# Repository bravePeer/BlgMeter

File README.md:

# BLGmeter
Device that can measure glucose in wort.

Used library to redirect website:
https://github.com/electronicsguy/HTTPSRedirect

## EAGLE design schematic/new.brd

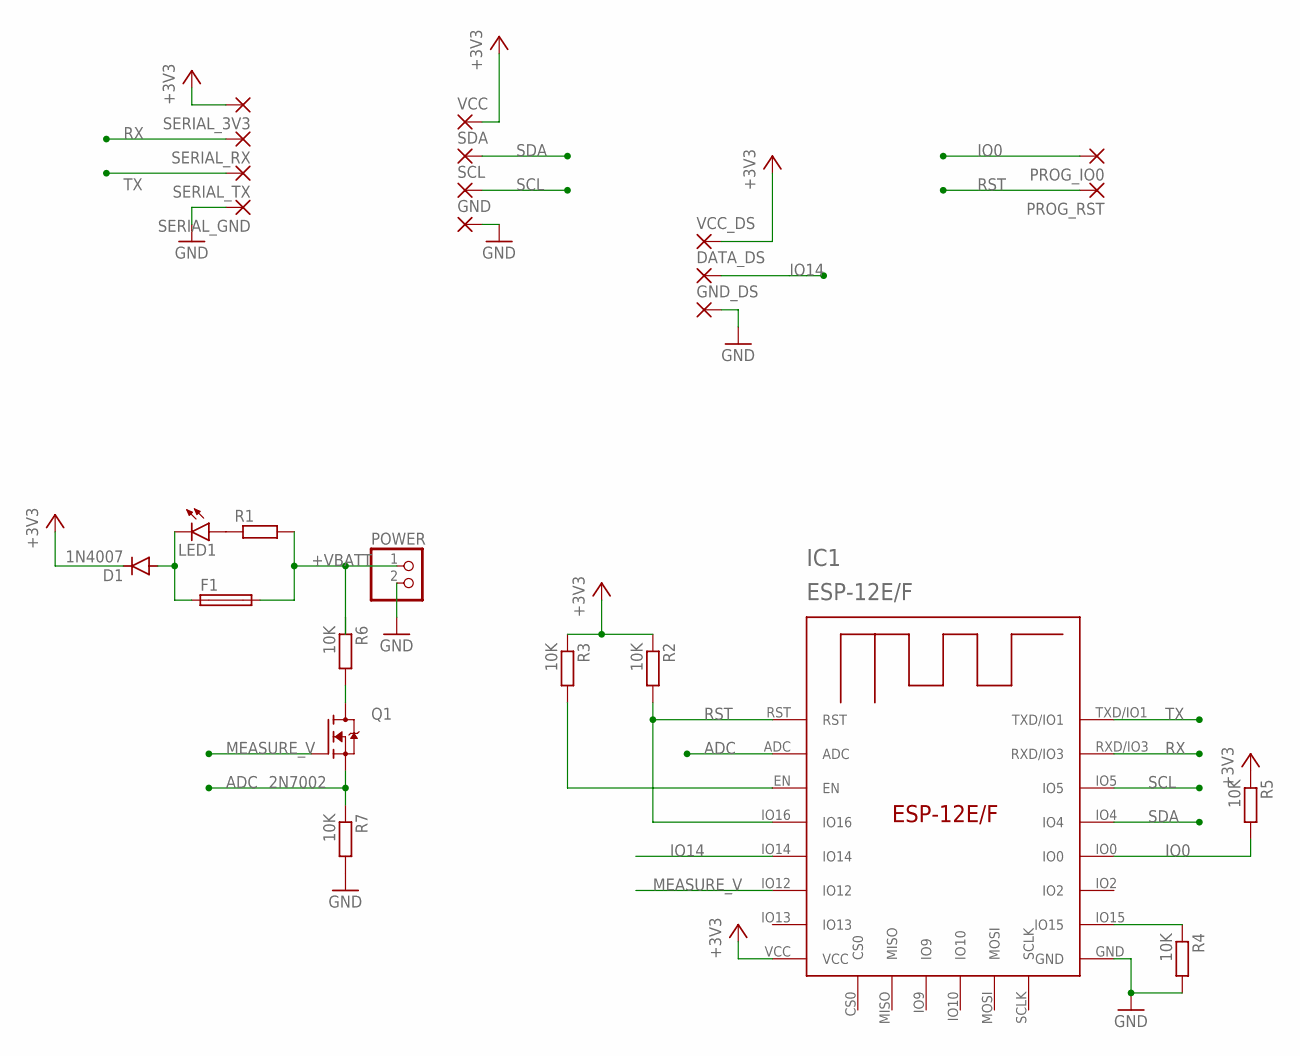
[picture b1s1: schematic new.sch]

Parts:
D1: 1N4007; DO35-7
DATA_DS: SMD2; SMD1,27-2,54
F1: 19560
GND: SMD2; SMD1,27-2,54
GND_DS: SMD2; SMD1,27-2,54
IC1: ESP-12E/F; ESP-12E
LED1: LEDSML0805; SML0805
POWER: PINHD-1X2; 1X02
PROG_IO0: SMD2; SMD1,27-2,54
PROG_RST: SMD2; SMD1,27-2,54
Q1: 2N7002; SOT95P240X111-3N
R1: R-EU_R0805; R0805
R2, R3, R4, R5, R6, R7: 10K; R0805
SCL: SMD2; SMD1,27-2,54
SDA: SMD2; SMD1,27-2,54
SERIAL_3V3: SMD2; SMD1,27-2,54
SERIAL_GND: SMD2; SMD1,27-2,54
SERIAL_RX: SMD2; SMD1,27-2,54
SERIAL_TX: SMD2; SMD1,27-2,54
VCC: SMD2; SMD1,27-2,54
VCC_DS: SMD2; SMD1,27-2,54

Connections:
+3V3: D1.C, IC1.VCC, R2.1, R3.1, R5.1, SERIAL_3V3.1, VCC.1, VCC_DS.1
+VBATT: F1.2, POWER.1, R1.2, R6.1
ADC: IC1.ADC, Q1.2 (S), R7.1
GND: GND.1, GND_DS.1, IC1.GND, POWER.2, R4.2, R7.2, SERIAL_GND.1
IO0: IC1.IO0, PROG_IO0.1, R5.2
IO14: DATA_DS.1, IC1.IO14
MEASURE_V: IC1.IO12, Q1.1 (G)
unnamed: LED1.A, R1.1
unnamed: Q1.3 (D), R6.2
unnamed: D1.A, F1.1, LED1.C
unnamed: IC1.EN, R3.2
unnamed: IC1.IO15, R4.1
RST: IC1.IO16, IC1.RST, PROG_RST.1, R2.2
RX: IC1.RXD/IO3, SERIAL_RX.1
SCL: IC1.IO5, SCL.1
SDA: IC1.IO4, SDA.1
TX: IC1.TXD/IO1, SERIAL_TX.1

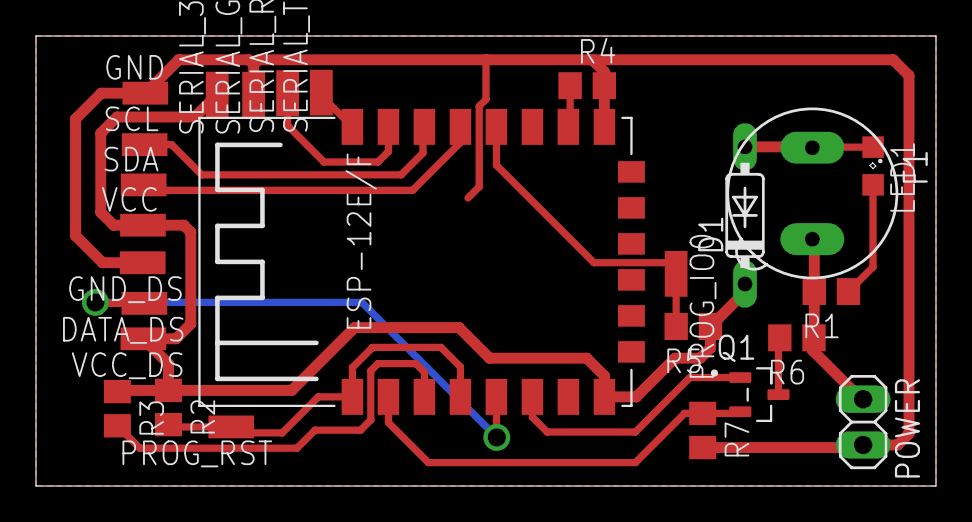
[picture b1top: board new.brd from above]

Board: 2 copper layers, 50.0 x 25.0 mm, 26 parts (0 on the bottom side), 17 nets.

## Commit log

2023-05-29 Add source control to project
2023-05-29 Add simple readme
2023-05-29 Sort files and add schematic
2023-06-14 Small fix
2023-06-14 update gitignore
2023-06-14 Add RTC menager
2023-06-15 Added send old data
2023-06-15 Add real sleep time
2023-06-16 Add device name to EEPROM
